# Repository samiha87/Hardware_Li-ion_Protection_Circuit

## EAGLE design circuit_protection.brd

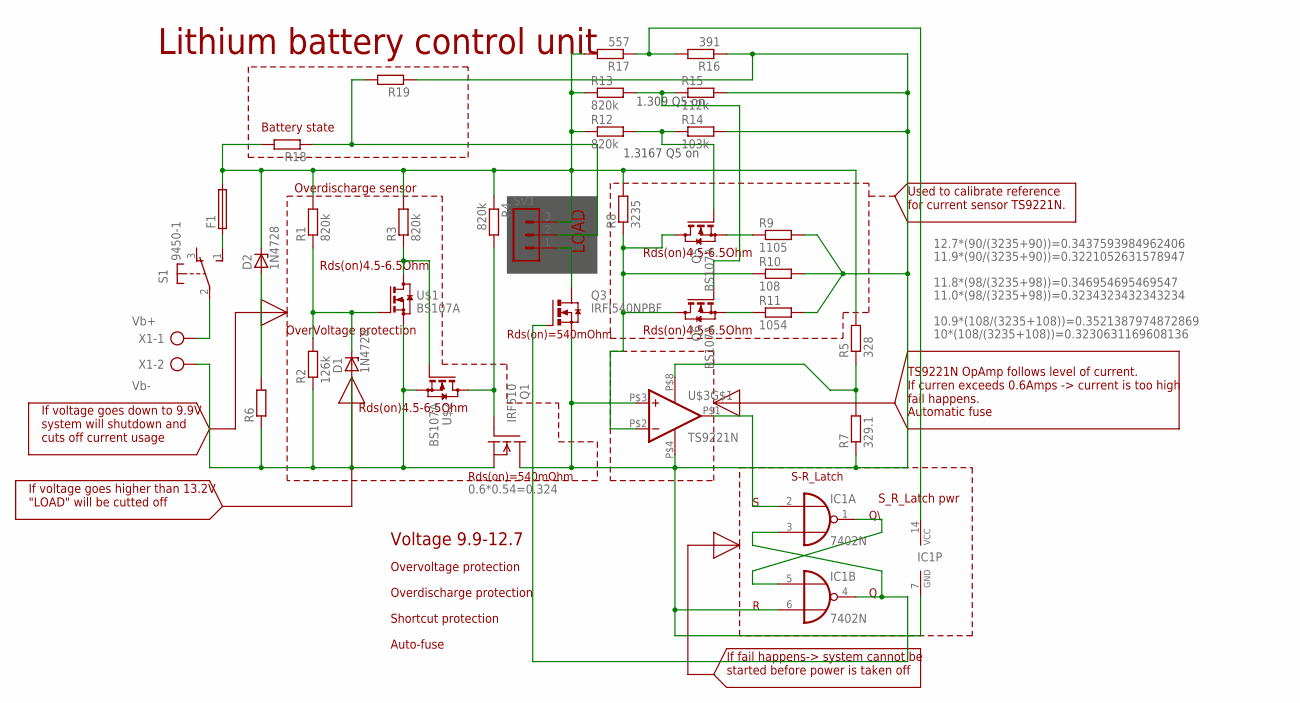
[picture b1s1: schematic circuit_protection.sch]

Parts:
D1, D2: 1N4728; DO41Z10
F1: GSH15
IC1: 7402N; DIL14
Q1: IRF510; TO220
Q3: IRFI540NPBF; TO220BH
Q5, Q6: BS107A; BC877
R1, R3, R4, R12, R13: 820k; 0204/7
R2: 126k; 0204/7
R5: 328; 0204/7
R6, R18, R19: R-EU_0204/7; 0204/7
R7: 329.1; 0204/7
R8: 3235; 0204/7
R9: 1105; 0204/7
R10: 108; 0204/7
R11: 1054; 0204/7
R14: 103k; 0204/7
R15: 112k; 0204/7
R16: 391; 0204/7
R17: 557; 0204/7
S1: 9450-1
SV1: MA03-1
U$1, U$2: BS107A; BC877
U$3: TS9221N; DIP08
X1: AK300/2

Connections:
820K: D1.C, R1.1, R2.2, U$1.2 (G)
BSTATE: R18.1, R19.2, SV1.2
GND: D1.A, Q1.3 (S), R2.1, R6.1, U$1.3 (S), U$2.3 (S), X1.2
GND2: IC1.6 (I1), IC1.7 (GND), Q1.2 (D), Q3.S, R7.1, R9.2, R10.2, R11.2, R14.2, R15.2, R16.1, R19.1, U$3.P$3 (+IN), U$3.P$4 (V-)
GND3: Q3.D, SV1.1
unnamed: D2.A, R6.2
unnamed: F1.1, S1.1 (S)
unnamed: IC1.3 (I1), IC1.4 (O), Q3.G
unnamed: R3.1, U$1.1 (D), U$2.2 (G)
unnamed: IC1.1 (O), IC1.5 (I0)
unnamed: IC1.2 (I0), U$3.P$1 (OUT)
unnamed: Q5.3 (S), R9.1
unnamed: Q5.2 (G), R12.2, R14.1
unnamed: Q6.2 (G), R13.2, R15.1
unnamed: Q5.1 (D), Q6.1 (D), R8.1, R10.1, U$3.P$2 (-IN)
unnamed: Q6.3 (S), R11.1
OA-VCC+: R5.1, R7.2, U$3.P$8 (V+)
QG: Q1.1 (G), R4.2, U$2.1 (D)
S-R_LATCH+: IC1.14 (VCC), R16.2, R17.1
VB+: S1.2, X1.1
VCC: D2.C, F1.2, R1.2, R3.2, R4.1, R5.2, R8.2, R12.1, R13.1, R17.2, R18.2, SV1.3

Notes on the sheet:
Vb+
Vb-
LOAD
Voltage 9.9-12.7
Rds(on)=540mOhm
S-R_Latch
Lithium battery control unit
Overvoltage protection
Overdischarge protection
Shortcut protection
Auto-fuse
Rds(on)4.5-6.5Ohm
Battery state
S_R_Latch pwr
If fail happens-> system cannot be started before power is taken off
TS9221N OpAmp follows level of current. If curren exceeds 0.6Amps -> current is too high fail happens.
Automatic fuse
Overdischarge sensor
If voltage goes down to 9.9V system will shutdown and cuts off current usage
OverVoltage protection
If voltage goes higher than 13.2V "LOAD" will be cutted off
Used to calibrate reference for current sensor TS9221N.
0.6*0.54=0.324
12.7*(90/(3235+90))=0.3437593984962406
11.8*(98/(3235+98))=0.346954695469547
10*(108/(3235+108))=0.3230631169608136
11.0*(98/(3235+98))=0.3234323432343234
11.9*(90/(3235+90))=0.3221052631578947
10.9*(108/(3235+108))=0.3521387974872869
1.309 Q5 on
1.3167 Q5 on

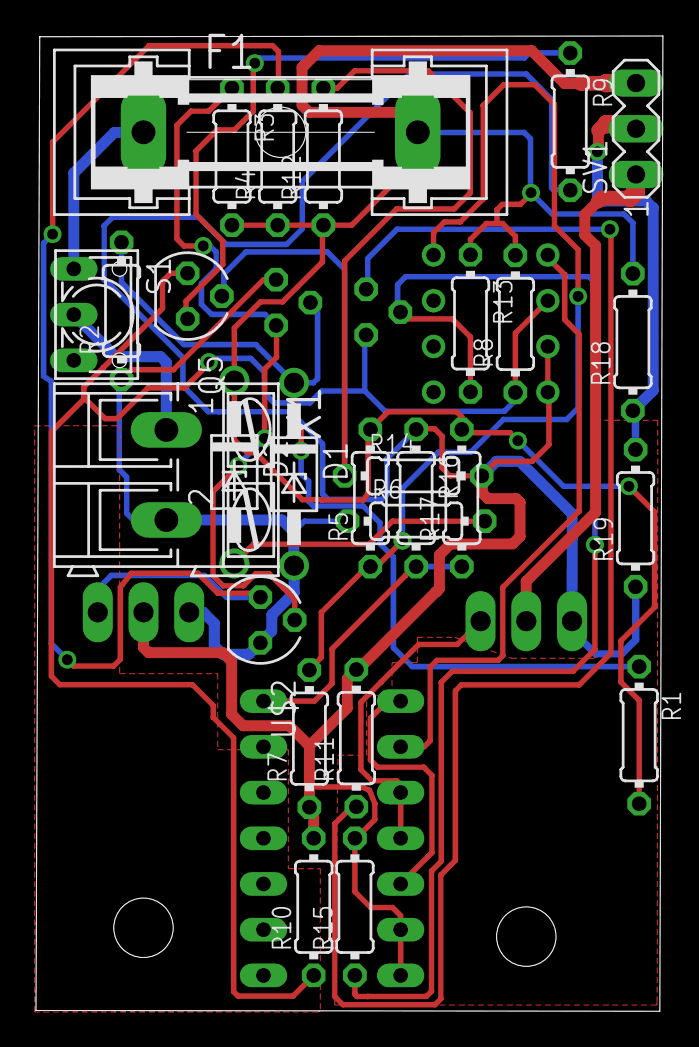
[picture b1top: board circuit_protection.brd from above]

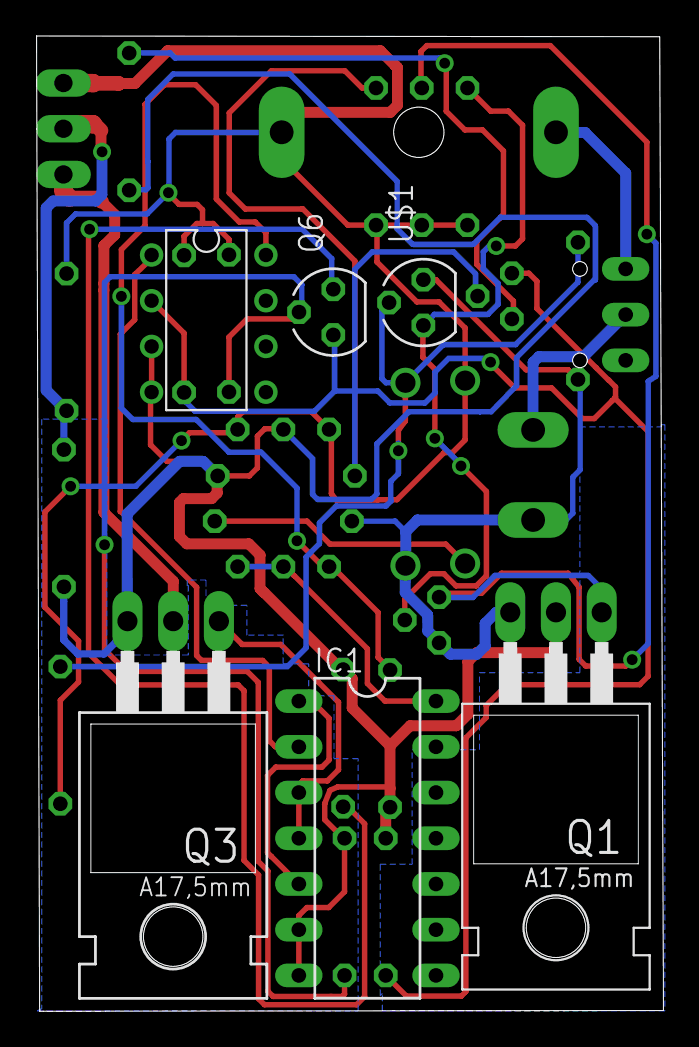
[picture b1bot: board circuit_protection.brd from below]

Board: 2 copper layers, 34.8 x 54.2 mm, 33 parts (6 on the bottom side), 21 nets.

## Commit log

2019-08-24 Li-ion protection circuit
